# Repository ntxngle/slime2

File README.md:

# slime2
## What and Why

A ESP8266 based SlimeVR tracker with all of the features of the much bigger and cumbersome official/DIY ones.

A friend introduced me to these trackers by building his own. He had purchased the many modules off of aliexpress and him, a friend, and myself gathered at my house to solder them. Apart from the legendary "soldering party" (fumes included) that subsequently happened, we managed to solder together the modules on a carrier board, with the occasional wire jumper when things went wrong. To me, the whole project seemed silly. Why buy IMU, Devboard, and charging modules when all of these can be integrated on one board? Cost for one. But with a little skill you can drastically reduce price by soldering it yourself. Thus began the development of slime2.

It's important to note that there are many like it. But this one is mine. VR and full body tracking attracts many CS types (for worse, not better), and thus many people have tried (and succeeded) to build custom trackers/modules/carriers etc. Regardless, many aimed for the degenerate maximization of battey life to support their double digit hour sessions, and not size. I am doing the opposite. 

Another important execption: it uses Wifi. There are slimevr trackers that use ESB on nRF modules that are the same size and last 10x longer, but are 10x as expensive.

As as result, I present the Wifi SlimeVR tracker with an area 13% than that of a credit card. 

## Tuff photos

## How it works

It uses SlimeVR firmware extactly like the normal trackers, and interfaces with pretty much the same hardware/pins, it's just that instead of being modules connected to modules, everything is already mounted to PCB.

## BOM
This bom makes one tracker. repeat as needed.

|Name            |Quantity|Footprint                             |LCSC Id  |Cost (with MOQ)|
|----------------|--------|--------------------------------------|---------|---------------|
|PCB             |1       |                                      |JLCPCB, files in repo|2              |
|Battery         |1       |                                      |https://es.aliexpress.com/item/1005012320035574.html|6              |
|Strap           |1       |                                      |https://es.aliexpress.com/item/1005005306808140.html|7.40           |
|SOICbite clip   |1       |                                      |https://es.aliexpress.com/item/1005005306808140.html|0.99           |
|10k             |5       |R_0402_1005Metric                     |https://www.lcsc.com/product-detail/C60490.html   |0.13           |
|2.2k            |2       |R_0402_1005Metric                     |https://www.lcsc.com/product-detail/C2906865.html |0.16           |
|ESP-WROOM-02    |1       |ESP-WROOM-02                          |https://www.lcsc.com/product-detail/C81770.html   |1.60           |
|HX MINI MSK12CO2|1       |SW-SMD_MSK12CO2                       |https://www.lcsc.com/product-detail/C5149840.html |0.77           |
|MCP73831-2-OT   |1       |SOT-23-5                              |https://www.lcsc.com/product-detail/C424093.html  |0.78           |
|ICM-45686       |1       |LGA-14_3x2.5mm_P0.5mm_LayoutBorder3x4y|https://www.lcsc.com/product-detail/C22459454.html|5.26           |
|180k            |1       |R_0402_1005Metric                     |https://www.lcsc.com/product-detail/C25760.html   |0.11           |
|HT7833          |1       |SOT-89-3                              |https://www.lcsc.com/product-detail/C50936.html   |1.66           |
|0.1uF           |5       |C_0402_1005Metric                     |https://www.lcsc.com/product-detail/C100072.html  |0.34           |
|LED             |2       |LED_0402_1005Metric                   |https://www.lcsc.com/product-detail/C21260817.html|0.58           |
|22uF            |1       |C_0402_1005Metric                     |https://www.lcsc.com/product-detail/C415703.html  |1.07           |
|10uF            |1       |C_0402_1005Metric                     |https://www.lcsc.com/product-detail/C7472949.html |0.64           |
|4.7uF           |1       |C_0402_1005Metric                     |https://www.lcsc.com/product-detail/C318563.html  |0.33           |
|2.7k            |1       |R_0402_1005Metric                     |https://www.lcsc.com/product-detail/C2906905.html |0.14           |
|Total| | | |31.92|

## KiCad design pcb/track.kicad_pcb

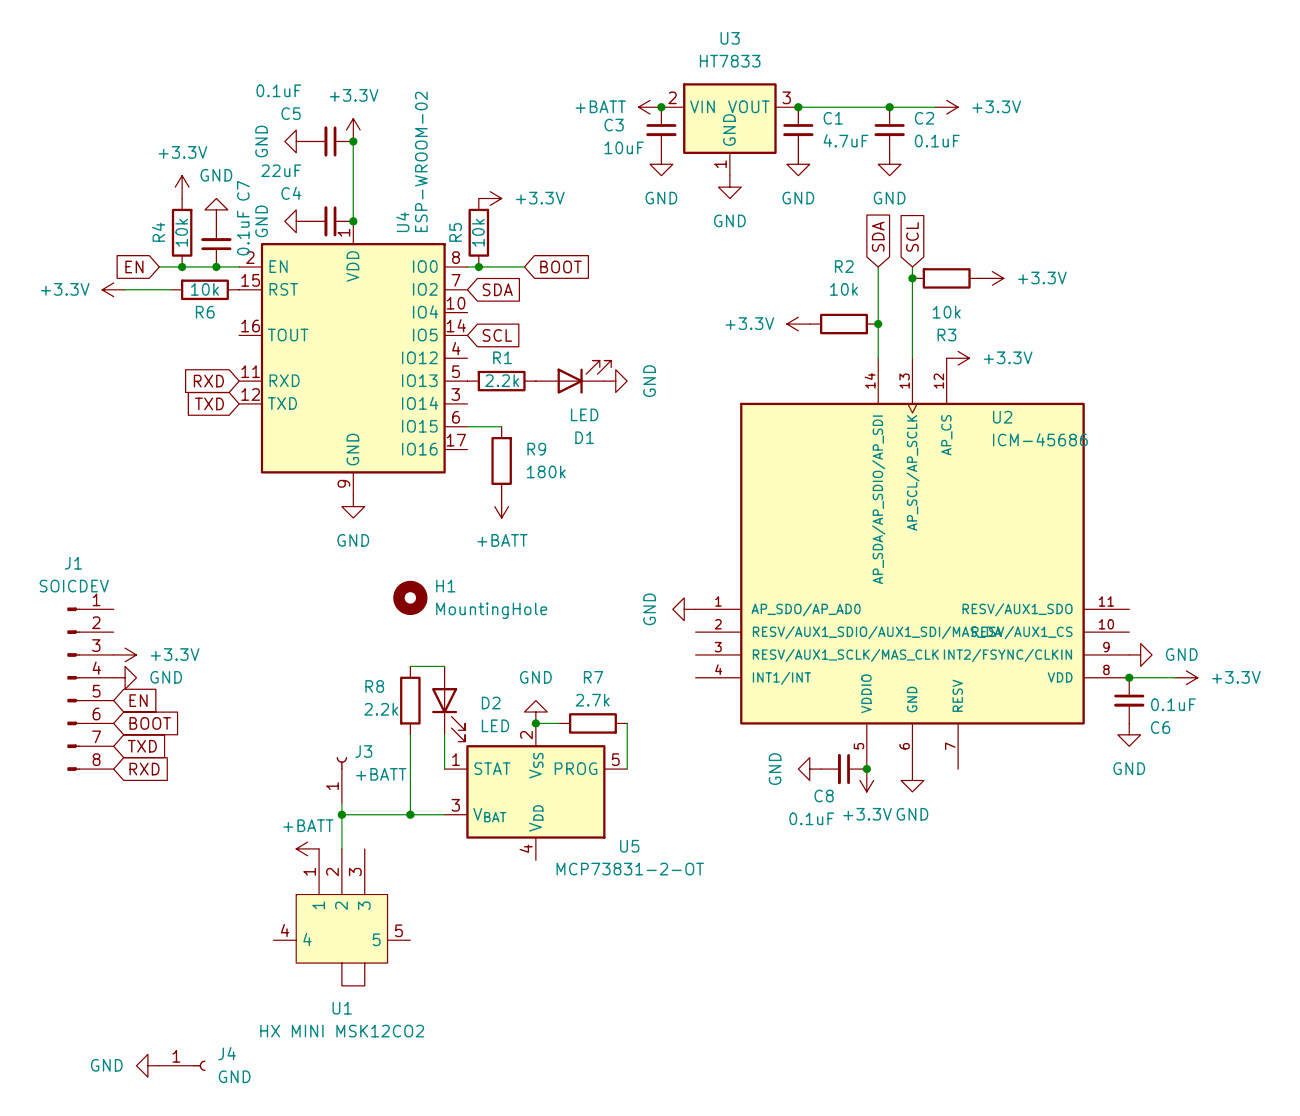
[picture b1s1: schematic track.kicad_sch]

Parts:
C1: 4.7uF; C_0402_1005Metric
C2, C5, C6, C7, C8: 0.1uF; C_0402_1005Metric
C3: 10uF; C_0402_1005Metric
C4: 22uF; C_0402_1005Metric
D1, D2: LED; LED_0402_1005Metric
H1: MountingHole; MountingHole_2.2mm_M2
J1: SOICDEV; SOIC_clipProgSmall
J3: +BATT; TestPoint_Pad_2.0x2.0mm
J4: GND; TestPoint_Pad_2.0x2.0mm
R1, R8: 2.2k; R_0402_1005Metric
R2, R3, R4, R5, R6: 10k; R_0402_1005Metric
R7: 2.7k; R_0402_1005Metric
R9: 180k; R_0402_1005Metric
U1: HX MINI MSK12CO2; SW-SMD_MSK12CO2; LCSC Part C5149840
U2: ICM-45686; LGA-14_3x2.5mm_P0.5mm_LayoutBorder3x4y; PARTREV 0.2
U3: HT7833; SOT-89-3
U4: ESP-WROOM-02
U5: MCP73831-2-OT; SOT-23-5

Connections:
+3.3V: C1.1, C2.1, C4.1, C5.1, C6.1, C8.1, J1.3, R2.1, R3.1, R4.2, R5.2, R6.2, U2.5 (VDDIO), U2.8 (VDD), U2.12 (AP_CS), U3.3 (VOUT), U4.1 (VDD)
+BATT: C3.1, R9.1, U1.1, U3.2 (VIN)
BOOT: J1.6, R5.1, U4.8 (IO0)
EN: C7.1, J1.5, R4.1, U4.2 (EN)
GND: C1.2, C2.2, C3.2, C4.2, C5.2, C6.2, C7.2, C8.2, D1.1 (K), J1.4, J4.1, R7.1, U2.1 (AP_SDO/AP_AD0), U2.6 (GND), U2.9 (INT2/FSYNC/CLKIN), U3.1 (GND), U4.9 (GND), U4.13 (GND), U4.18 (GND), U4.19 (GND), U5.2 (V_{SS})
unnamed: D1.2 (A), R1.1
unnamed: D2.2 (A), R8.1
unnamed: D2.1 (K), U5.1 (STAT)
unnamed: J3.1, R8.2, U1.2, U5.3 (V_{BAT})
unnamed: R1.2, U4.5 (IO13)
unnamed: R9.2, U4.6 (IO15)
unnamed: R6.1, U4.15 (RST)
unnamed: R7.2, U5.5 (PROG)
RXD: J1.8, U4.11 (RXD)
SCL: R3.2, U2.13 (AP_SCL/AP_SCLK), U4.14 (IO5)
SDA: R2.2, U2.14 (AP_SDA/AP_SDIO/AP_SDI), U4.7 (IO2)
TXD: J1.7, U4.12 (TXD)

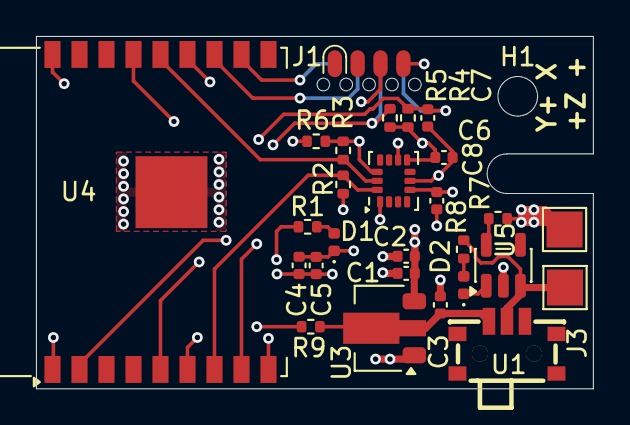
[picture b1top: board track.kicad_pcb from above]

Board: 4 copper layers, 30.9 x 19.6 mm, 28 parts (0 on the bottom side), 17 nets.

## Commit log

2026-06-21 larp
2026-06-25 larp idiot
